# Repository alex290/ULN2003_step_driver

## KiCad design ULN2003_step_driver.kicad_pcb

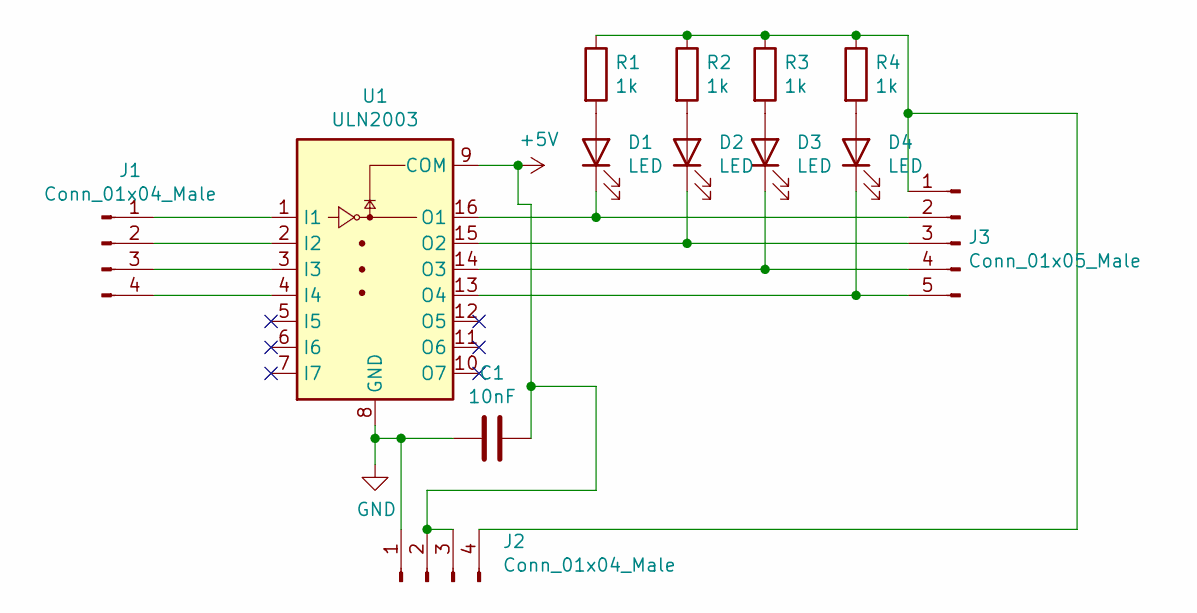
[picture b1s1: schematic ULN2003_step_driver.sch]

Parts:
C1: 10nF; C_Disc_D3.0mm_W2.0mm_P2.50mm
D1, D2, D3, D4: LED; LED_D5.0mm
J1, J2: Conn_01x04_Male; PinHeader_1x04_P2.54mm_Vertical
J3: Conn_01x05_Male; JST_XH_B5B-XH-A_1x05_P2.50mm_Vertical
R1, R2, R3, R4: 1k; R_Axial_DIN0207_L6.3mm_D2.5mm_P7.62mm_Horizontal
U1: ULN2003; DIP-16_W7.62mm_Socket

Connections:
+5V: C1.1, J2.2, J2.3, U1.9 (COM)
GND: C1.2, J2.1, U1.8 (GND)
unnamed: D1.1 (K), J3.2, U1.16 (O1)
unnamed: D1.2 (A), R1.2
unnamed: D2.1 (K), J3.3, U1.15 (O2)
unnamed: D2.2 (A), R2.2
unnamed: D3.1 (K), J3.4, U1.14 (O3)
unnamed: D3.2 (A), R3.2
unnamed: D4.1 (K), J3.5, U1.13 (O4)
unnamed: D4.2 (A), R4.2
unnamed: J1.1, U1.1 (I1)
unnamed: J1.2, U1.2 (I2)
unnamed: J1.3, U1.3 (I3)
unnamed: J1.4, U1.4 (I4)
unnamed: J2.4, J3.1, R1.1, R2.1, R3.1, R4.1

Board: 2 copper layers, 13 parts (0 on the bottom side), 15 nets, no tracks yet.
